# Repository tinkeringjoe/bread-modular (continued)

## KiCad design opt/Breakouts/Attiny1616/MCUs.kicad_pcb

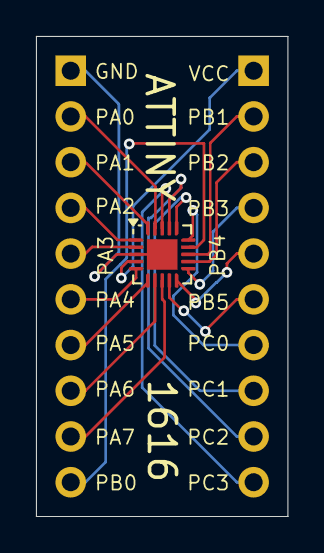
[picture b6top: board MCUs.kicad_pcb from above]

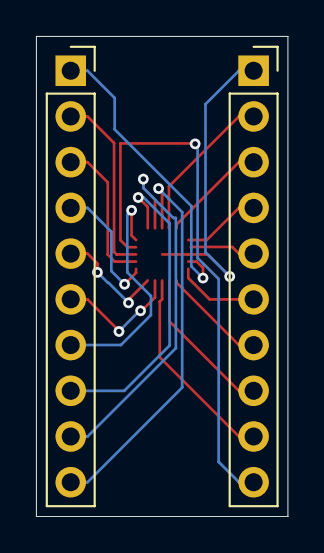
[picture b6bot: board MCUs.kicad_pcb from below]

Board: 2 copper layers, 14.0 x 26.7 mm, 3 parts (2 on the bottom side), 20 nets.

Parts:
J1: LEFT; PinSocket_1x10_P2.54mm_Vertical
J2: RIGHT; PinSocket_1x10_P2.54mm_Vertical
U1: ATtiny1616-M; VQFN-20-1EP_3x3mm_P0.4mm_EP1.7x1.7mm

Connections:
GND: J1.1, U1.3 (GND), U1.21 (GND)
unnamed: J1.2, U1.19 (~RESET/PA0)
unnamed: J1.3, U1.20 (PA1)
unnamed: J1.4, U1.1 (PA2)
unnamed: J1.5, U1.2 (PA3)
unnamed: J1.6, U1.5 (PA4)
unnamed: J1.7, U1.6 (PA5)
unnamed: J1.8, U1.7 (PA6)
unnamed: J1.9, U1.8 (PA7)
unnamed: J1.10, U1.14 (PB0)
unnamed: J2.2, U1.13 (PB1)
unnamed: J2.3, U1.12 (PB2)
unnamed: J2.4, U1.11 (PB3)
unnamed: J2.5, U1.10 (PB4)
unnamed: J2.6, U1.9 (PB5)
PC0: J2.7, U1.15 (PC0)
PC1: J2.8, U1.16 (PC1)
PC2: J2.9, U1.17 (PC2)
PC3: J2.10, U1.18 (PC3)
VCC: J2.1, U1.4 (VCC)
